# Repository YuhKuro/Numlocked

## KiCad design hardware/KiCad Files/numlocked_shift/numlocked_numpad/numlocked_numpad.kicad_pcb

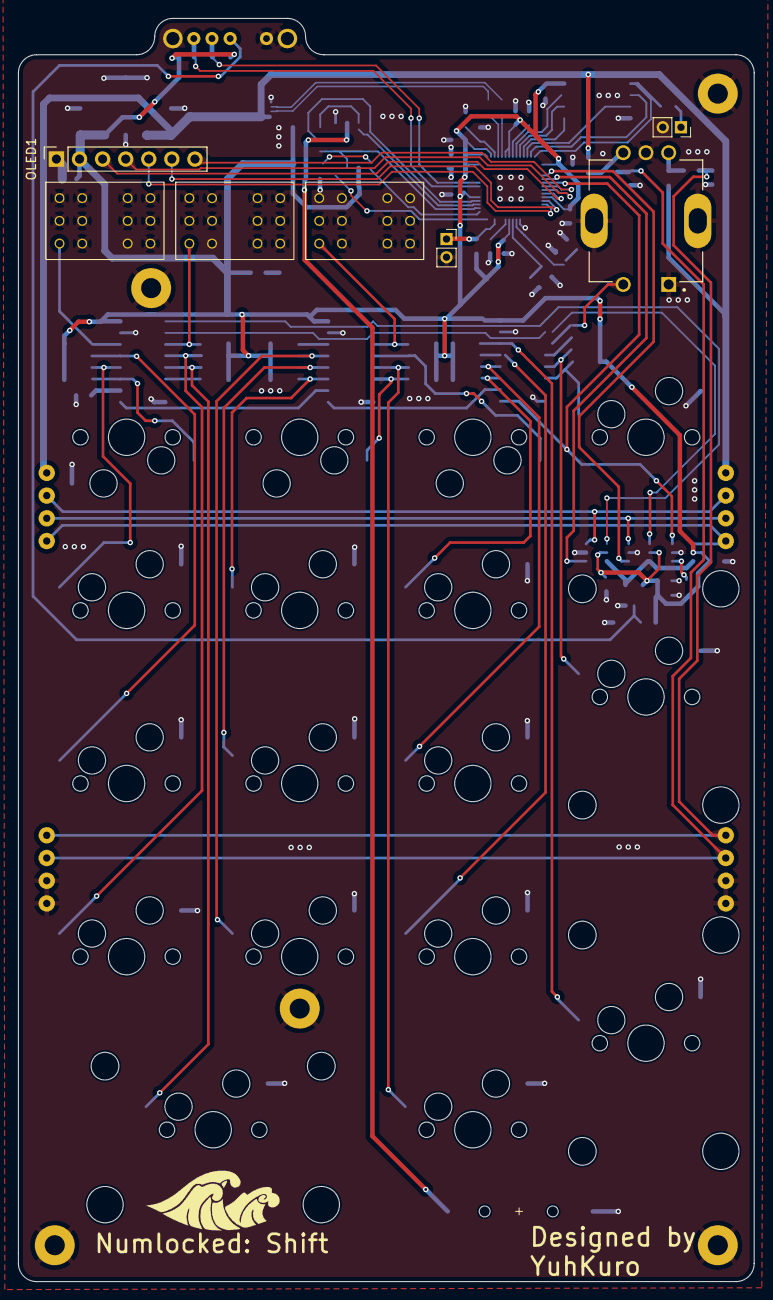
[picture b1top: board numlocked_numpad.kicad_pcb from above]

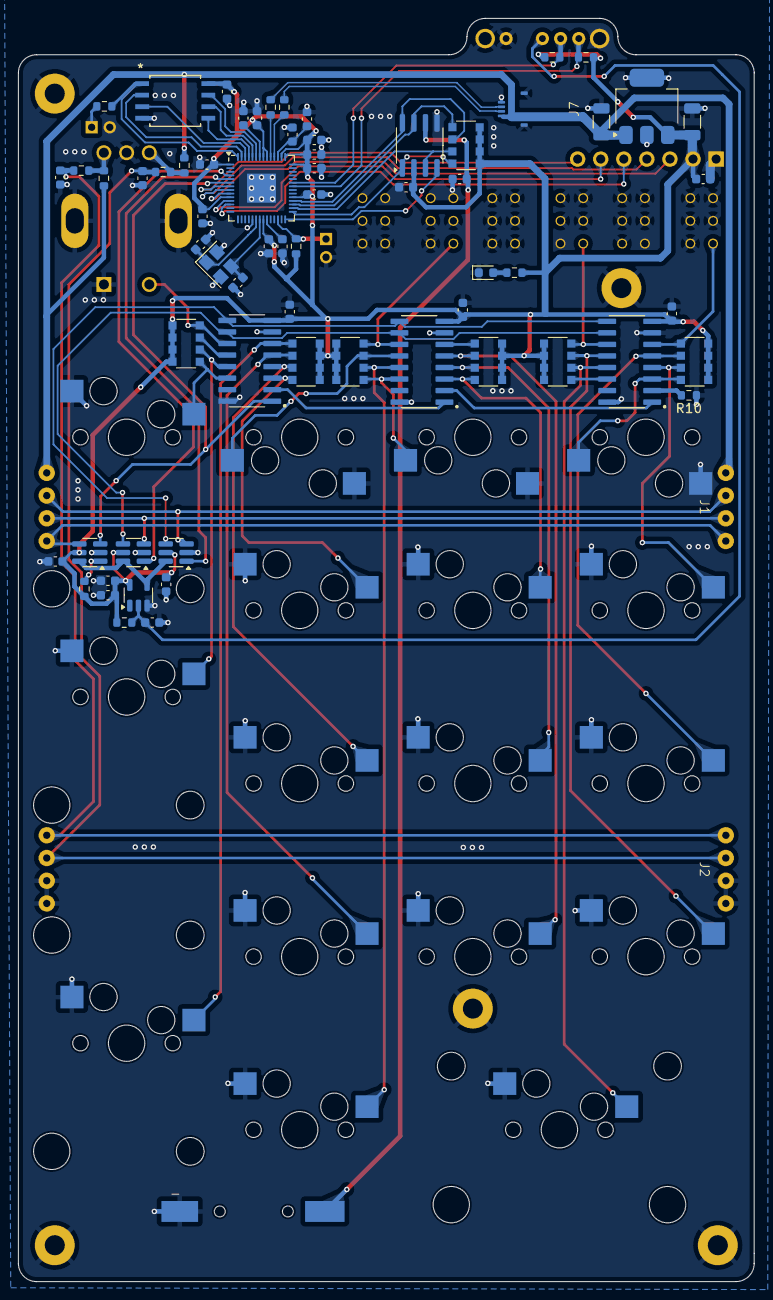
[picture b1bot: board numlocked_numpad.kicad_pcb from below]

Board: 4 copper layers, 81.0 x 139.0 mm, 100 parts (68 on the bottom side), 74 nets.

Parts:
BT1: Battery_Cell; Q&J CR1220-2
C1, C5: 0.01 μF; C_0603_1608Metric
C2, C3, C4, C9, C12, C13, C14, C17, C18, C19, C20, C21, C22, C23, C24, C25, C26, C27, C28, C29, C31, C32: 0.1 uF; C_0603_1608Metric
C6: 0.47 uF; C_1206_3216Metric
C7: 33 uF; C_1206_3216Metric
C10, C11: 18 pF; C_0603_1608Metric
C15, C16: 1 uF; C_0603_1608Metric
D1: LED Power; LED_0603_1608Metric
H1, H2, H4, H5, H6: MountingHole_Pad; MountingHole_2.2mm_M2_Pad
J1, J2, J3, J4: Conn_01x04; Magnetic_Pogo_Pin_4pos
J5, J6: Conn_01x02; PinSocket_1x02_P2.00mm_Vertical
J7: AYF530435
MT1: PEC11R-4215F-S0024; XDCR_PEC11R-4215F-S0024
OLED1: PinSocket_1x07_P2.54mm_Vertical
R1, R2, R3, R4, R6, R7, R12, R13, R14: 10k; R_0603_1608Metric
R5: 240; R_0603_1608Metric
R8, R9: 27; R_0603_1608Metric
R10: 0; R_0603_1608Metric
R11: 1K; R_0603_1608Metric
RN1, RN2, RN3, RN4, RN5, RN6, RN7: 10K; R_Array_Convex_4x1206
S1, S2, S3, S6, S8, S9, S10, S11, S12, S14, S16, S17, S18, S19: SW_Cherry_Kalih_1.00u
S7: SW_Cherry_Kalih_2.00u
S15, S20: SW_Cherry_Kalih_2.00u_vert
SW1: SK13D07VG4
SW2, SW3, SW4: MHPS4284
U1: LM3940IMP-3.3/NOPB; SOT-223
U2, U3, U4: SN74HC165DR
U5, U9, U10: SC-74-6_1.55x2.9mm_P0.95mm
U6: RP2040; QFN-56-1EP_7x7mm_P0.4mm_EP3.2x3.2mm
U7: W25Q128JVSIQ; SOIC_128JVSIQ_WIN
U8: 74LVC1G17; SOT-23-5
U11: DS3231MZ; SOIC-8_3.9x4.9mm_P1.27mm
X1: ABM8G-12.000MHZ-18-D2Y-T; Crystal_SMD_Abracon_ABM8AIG-4Pin_3.2x2.5mm

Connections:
+1V1: C12.1, C13.1, C14.1, C15.1, U6.23 (DVDD), U6.45 (VREG_VOUT), U6.50 (DVDD)
+3V3: C2.1, C3.1, C4.1, C7.1, C9.1, C16.1, C17.1, C18.1, C19.1, C20.1, C21.1, C22.1, C23.1, C24.1, C26.1, C27.1, C28.1, C29.1, C31.1, OLED1.2 (VCC), R5.1, R6.2, R7.2, R12.2, R13.2, R14.2, RN1.5 (R4.2), RN1.6 (R3.2), RN1.7 (R2.2), RN1.8 (R1.2), RN2.5 (R4.2), RN2.6 (R3.2), RN2.7 (R2.2), RN2.8 (R1.2), RN3.5 (R4.2), RN3.6 (R3.2), RN3.7 (R2.2), RN3.8 (R1.2), RN4.5 (R4.2), RN4.6 (R3.2), RN4.7 (R2.2), RN4.8 (R1.2), RN5.5 (R4.2), RN5.6 (R3.2), RN5.7 (R2.2), RN5.8 (R1.2), RN6.5 (R4.2), RN6.6 (R3.2), RN6.7 (R2.2), RN6.8 (R1.2), RN7.1 (R1.1), RN7.2 (R2.1), RN7.3 (R3.1), RN7.4 (R4.1), U1.3 (OUT), U2.16 (VCC), U3.16 (VCC), U4.16 (VCC), U5.5 (VCC), U6.1 (IOVDD), U6.10 (IOVDD), U6.22 (IOVDD), U6.33 (IOVDD), U6.42 (IOVDD), U6.43 (ADC_AVDD), U6.44 (VREG_IN), U6.48 (USB_VDD), U6.49 (IOVDD), U7.8 (VCC), U8.5 (VCC), U9.5 (VCC), U10.5 (VCC), U11.2 (VCC)
+5V: C6.1, J1.1, J3.1, J7.1, R1.1, R3.1, U1.1 (IN)
/CLK: U2.2 (CLK), U3.2 (CLK), U4.2 (CLK), U10.4 (Y)
/Encoder A: C1.1, J2.1, J4.1, R2.1
/Encoder B: C5.1, J2.2, J4.2, R4.1
/ModeSwitch1: R13.1, SW1.3, U6.37 (GPIO25)
/ModeSwitch2: R12.1, SW1.4, U6.36 (GPIO24)
/QSPI_SCLK: U6.52 (QSPI_SCLK), U7.6 (CLK)
/QSPI_SD0: U6.53 (QSPI_SD0), U7.5 (DI(IO0))
/QSPI_SD1: U6.55 (QSPI_SD1), U7.2 (DO(IO1))
/QSPI_SD2: U6.54 (QSPI_SD2), U7.3 (/WP(IO2))
/QSPI_SD3: U6.51 (QSPI_SD3), U7.7 (/HOLD/RESET(IO3))
/QSPI_SS: R11.2, U6.56 (QSPI_SS), U7.1 (/CS)
/RTC_32KHZ: RN7.8 (R1.2), U6.29 (GPIO18), U11.1 (32KHZ)
/RTC_SCL: RN7.6 (R3.2), U6.32 (GPIO21), U11.8 (SCL)
/RTC_SDA: RN7.5 (R4.2), U6.31 (GPIO20), U11.7 (SDA)
/SH: U2.1 (SH/~LD), U3.1 (SH/~LD), U4.1 (SH/~LD), U9.4 (Y)
/SSD1112 CS: OLED1.7 (CS), U6.7 (GPIO5)
/SSD1112 DC: OLED1.6 (DC), U6.11 (GPIO8)
/SSD1112 RST: OLED1.5 (RST), U6.12 (GPIO9)
/SSD1112 SDA: OLED1.4 (SDA), U6.8 (GPIO6)
/SSD1122 SCL: OLED1.3 (SCL), U6.9 (GPIO7)
/SerialOut: U4.9 (QH), U5.3 (I0), U6.6 (GPIO4)
/Serialout-Numpad: J1.4, J3.4, U5.4 (Y)
/USB_RP2040+: J7.3, R8.1
/USB_RP2040-: J7.2, R9.1
/USB_RP2040_Res+: R8.2, U6.47 (USB_DP)
/USB_RP2040_Res-: R9.2, U6.46 (USB_DM)
/VBAT: BT1.1 (+), C32.1, U11.6 (VBAT)
/XIN: C10.2, U6.20 (XIN), X1.1
/XOUT: C11.2, U6.21 (XOUT), X1.3
/keyboardCLK: J1.3, J3.3, U10.3 (I0)
/keyboardSH: J1.2, J3.2, U9.3 (I0)
/numpadCLK: U6.4 (GPIO2), U10.1 (I1)
/numpadSH: U6.5 (GPIO3), U9.1 (I1)
/~RTC_INT: RN7.7 (R2.2), U6.30 (GPIO19), U11.3 (~INT/SQW)
/~RTC_RST: U6.28 (GPIO17), U11.4 (~RST)
/~USB BOOT: J5.1, R11.1
/~reset: J6.1, R7.1, U6.26 (RUN)
GND: BT1.2 (-), C1.2, C2.2, C3.2, C4.2, C5.2, C6.2, C7.2, C9.2, C10.1, C11.1, C12.2, C13.2, C14.2, C15.2, C16.2, C17.2, C18.2, C19.2, C20.2, C21.2, C22.2, C23.2, C24.2, C25.2, C26.2, C27.2, C28.2, C29.2, C31.2, C32.2, D1.1 (K), H1.1, H2.1, H4.1, H5.1, H6.1, J2.3, J2.4, J4.3, J4.4, J5.2, J6.2, J7.4, J7.P1, J7.P2, MT1.1, MT1.COM, MT1.S1 (SHIELD), MT1.S2 (SHIELD__1), OLED1.1 (GND), R10.1, S1.2, S2.2, S3.2, S6.2, S7.2, S8.2, S9.2, S10.2, S11.2, S12.2, S14.2, S15.2, S16.2, S17.2, S18.2, S19.2, S20.2, SW1.1, SW1.MNT1, SW1.MNT2, SW2.1 (NC), SW2.3 (GND), SW3.1 (NC), SW3.3 (GND), SW4.1 (NC), SW4.3 (GND), U1.2 (GND), U1.4 (GND), U2.8 (GND), U2.15 (CLK_INH), U3.8 (GND), U3.15 (CLK_INH), U4.8 (GND), U4.15 (CLK_INH), U5.2 (GND), U6.19 (TESTEN), U6.57 (GND), U7.4 (GND), U8.3 (GND), U9.2 (GND), U10.2 (GND), U11.5 (GND), X1.2, X1.4
unnamed: C25.1, R14.1, SW1.2, U8.2
unnamed: D1.2 (A), R5.2
unnamed: MT1.A, R1.2, R2.2
unnamed: MT1.B, R3.2, R4.2
unnamed: RN1.1 (R1.1), SW2.2 (NO), U2.14 (D)
unnamed: RN1.2 (R2.1), S3.1, U2.13 (C)
unnamed: RN1.3 (R3.1), S2.1, U2.12 (B)
unnamed: RN1.4 (R4.1), S1.1, U2.11 (A)
unnamed: RN2.1 (R1.1), U2.6 (H)
unnamed: RN2.2 (R2.1), S7.1, U2.5 (G)
unnamed: RN2.3 (R3.1), S6.1, U2.4 (F)
unnamed: RN2.4 (R4.1), SW3.2 (NO), U2.3 (E)
unnamed: RN3.1 (R1.1), U3.14 (D)
unnamed: RN3.2 (R2.1), S11.1, U3.13 (C)
unnamed: RN3.3 (R3.1), S10.1, U3.12 (B)
unnamed: RN3.4 (R4.1), S9.1, U3.11 (A)
unnamed: RN4.1 (R1.1), S8.1, U3.6 (H)
unnamed: RN4.2 (R2.1), S12.1, U3.5 (G)
unnamed: RN4.3 (R3.1), S14.1, U3.4 (F)
unnamed: RN4.4 (R4.1), SW4.2 (NO), U3.3 (E)
unnamed: RN5.1 (R1.1), S20.1, U4.14 (D)
unnamed: RN5.2 (R2.1), S19.1, U4.13 (C)
unnamed: RN5.3 (R3.1), S18.1, U4.12 (B)
unnamed: RN5.4 (R4.1), S17.1, U4.11 (A)
unnamed: RN6.1 (R1.1), S16.1, U4.6 (H)
unnamed: RN6.2 (R2.1), S15.1, U4.5 (G)
unnamed: RN6.3 (R3.1), U4.4 (F)
unnamed: MT1.2, RN6.4 (R4.1), U4.3 (E)
unnamed: U2.9 (QH), U3.10 (SER)
unnamed: R10.2, U2.10 (SER)
unnamed: U3.9 (QH), U4.10 (SER)
unnamed: R6.1, U5.1 (I1)
unnamed: U5.6 (S), U8.4, U9.6 (S), U10.6 (S)
